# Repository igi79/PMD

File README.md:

PMD 85 
by Peter Chrenko: http://pmd85.topindex.sk/

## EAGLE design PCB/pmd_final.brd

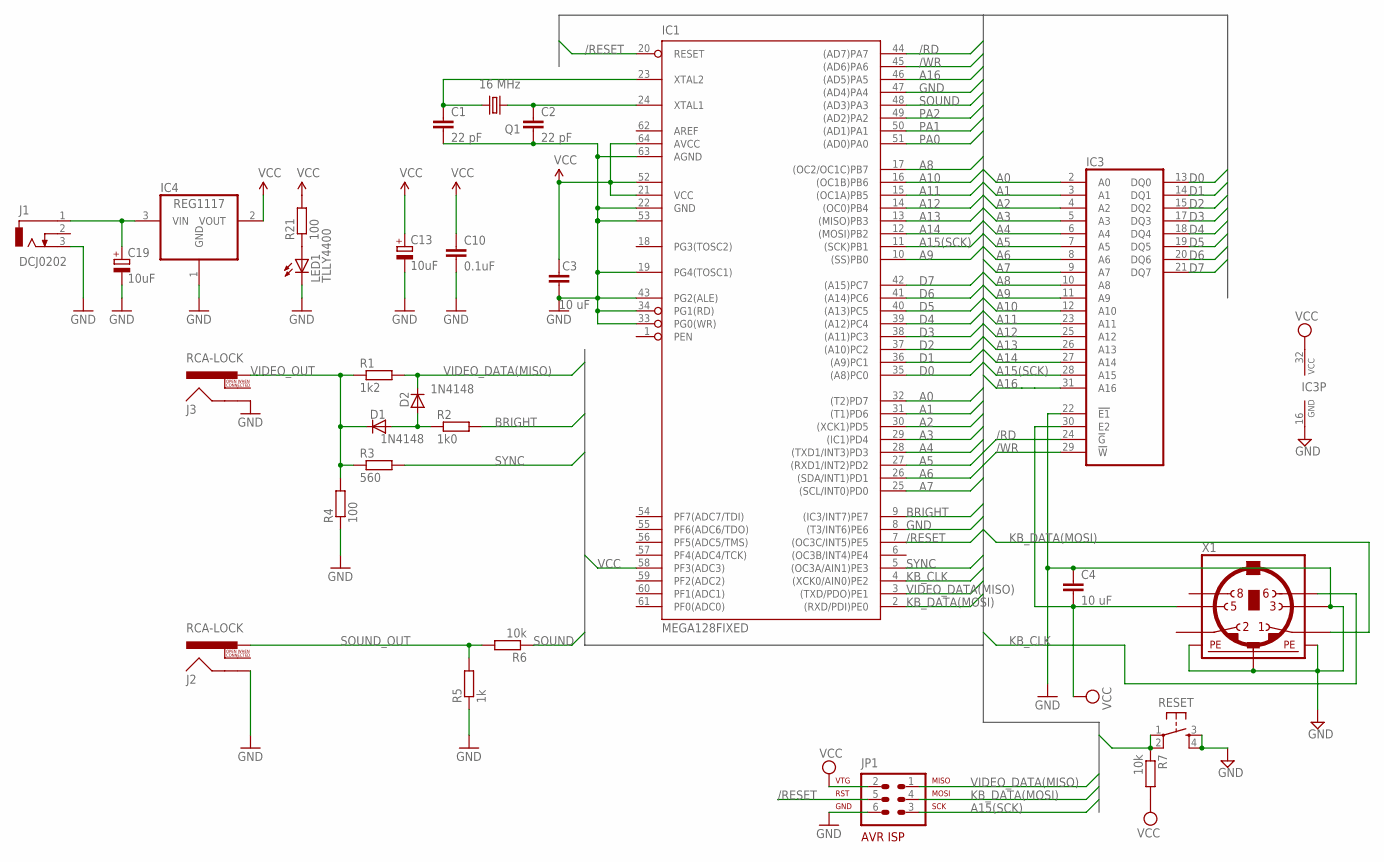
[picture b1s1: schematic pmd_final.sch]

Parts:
C1, C2: 22 pF; C0805
C3, C4: 10 uF; C0805
C10: 0.1uF; C0805
C13, C19: 10uF; E2,5-5
D1, D2: 1N4148; MINIMELF
IC1: MEGA128FIXED; TQFP64_14X14MM
IC3: MCM6226AULTRAWIDE; SOP32L
IC4: REG1117; SOT223
J1: DCJ0202
J2, J3: RCA-LOCK; RCA_LOCK
JP1: AVR-ISP-6R
LED1: TLLY4400; LED3MM
Q1: 16 MHz; HC49UP
R1: 1k2; R0805
R2: 1k0; R0805
R3: 560; R0805
R4, R21: 100; R0805
R5: 1k; R0805
R6, R7: 10k; R0805
RESET: RESET; TACTILE-PTH
X1: MINI_DIN_6; M_DIN6

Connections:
/RD: IC1.44 ((AD7)PA7), IC3.24 (!G)
/RESET: IC1.7 ((OC3C/INT5)PE5), IC1.20 (RESET), JP1.5, R7.1, RESET.1, RESET.2
/WR: IC1.45 ((AD6)PA6), IC3.29 (!W)
A0: IC1.32 ((T2)PD7), IC3.2 (A0)
A1: IC1.31 ((T1)PD6), IC3.3 (A1)
A2: IC1.30 ((XCK1)PD5), IC3.4 (A2)
A3: IC1.29 ((IC1)PD4), IC3.5 (A3)
A4: IC1.28 ((TXD1/INT3)PD3), IC3.6 (A4)
A5: IC1.27 ((RXD1/INT2)PD2), IC3.7 (A5)
A6: IC1.26 ((SDA/INT1)PD1), IC3.8 (A6)
A7: IC1.25 ((SCL/INT0)PD0), IC3.9 (A7)
A8: IC1.17 ((OC2/OC1C)PB7), IC3.10 (A8)
A9: IC1.10 ((SS)PB0), IC3.11 (A9)
A10: IC1.16 ((OC1B)PB6), IC3.12 (A10)
A11: IC1.15 ((OC1A)PB5), IC3.23 (A11)
A12: IC1.14 ((OC0)PB4), IC3.25 (A12)
A13: IC1.13 ((MISO)PB3), IC3.26 (A13)
A14: IC1.12 ((MOSI)PB2), IC3.27 (A14)
A15(SCK): IC1.11 ((SCK)PB1), IC3.28 (A15), JP1.3
A16: IC1.46 ((AD5)PA5), IC3.31 (A16)
BRIGHT: IC1.9 ((IC3/INT7)PE7), R2.2
D0: IC1.35 ((A8)PC0), IC3.13 (DQ0)
D1: IC1.36 ((A9)PC1), IC3.14 (DQ1)
D2: IC1.37 ((A10)PC2), IC3.15 (DQ2)
D3: IC1.38 ((A11)PC3), IC3.17 (DQ3)
D4: IC1.39 ((A12)PC4), IC3.18 (DQ4)
D5: IC1.40 ((A13)PC5), IC3.19 (DQ5)
D6: IC1.41 ((A14)PC6), IC3.20 (DQ6)
D7: IC1.42 ((A15)PC7), IC3.21 (DQ7)
GND: C1.2, C2.2, C3.1, C4.1, C10.2, C13.-, C19.-, IC1.8 ((T3/INT6)PE6), IC1.19 (PG4(TOSC1)), IC1.22 (GND), IC1.33 (PG0(WR)), IC1.34 (PG1(RD)), IC1.43 (PG2(ALE)), IC1.47 ((AD4)PA4), IC1.53 (GND1), IC1.63 (AGND), IC3.16 (GND), IC3.22 (!E1), IC4.1 (GND), J1.3, J2.SHELL, J3.SHELL, JP1.6, LED1.K (C), R4.1, R5.1, RESET.3, RESET.4, X1.3, X1.SH1 (PE1), X1.SH2 (PE2), X1.SH3 (PE3)
KB_CLK: IC1.4 ((XCK0/AIN0)PE2), X1.6
KB_DATA(MOSI): IC1.2 ((RXD/PDI)PE0), JP1.4, X1.1
unnamed: LED1.A, R21.1
unnamed: D1.A, D2.A, R2.1
PA0: IC1.51 ((AD0)PA0)
PA1: IC1.50 ((AD1)PA1)
PA2: IC1.49 ((AD2)PA2)
SOUND: IC1.48 ((AD3)PA3), R6.1
SOUND_OUT: J2.PIN, R5.2, R6.2
SYNC: IC1.5 ((OC3A/AIN1)PE3), R3.2
VCC: C3.2, C4.2, C10.1, C13.+, IC1.21 (VCC), IC1.52 (VCC1), IC1.58 (PF3(ADC3)), IC1.64 (AVCC), IC3.30 (E2), IC3.32 (VCC), IC4.2 (VOUT), JP1.2, R7.2, R21.2, X1.5
VIDEO_DATA(MISO): D2.C, IC1.3 ((TXD/PDO)PE1), JP1.1, R1.2
VIDEO_OUT: D1.C, J3.PIN, R1.1, R3.1, R4.2
VIN: C19.+, IC4.3 (VIN), J1.1
XTAL1: C2.1, IC1.24 (XTAL1), Q1.1
XTAL2: C1.1, IC1.23 (XTAL2), Q1.2

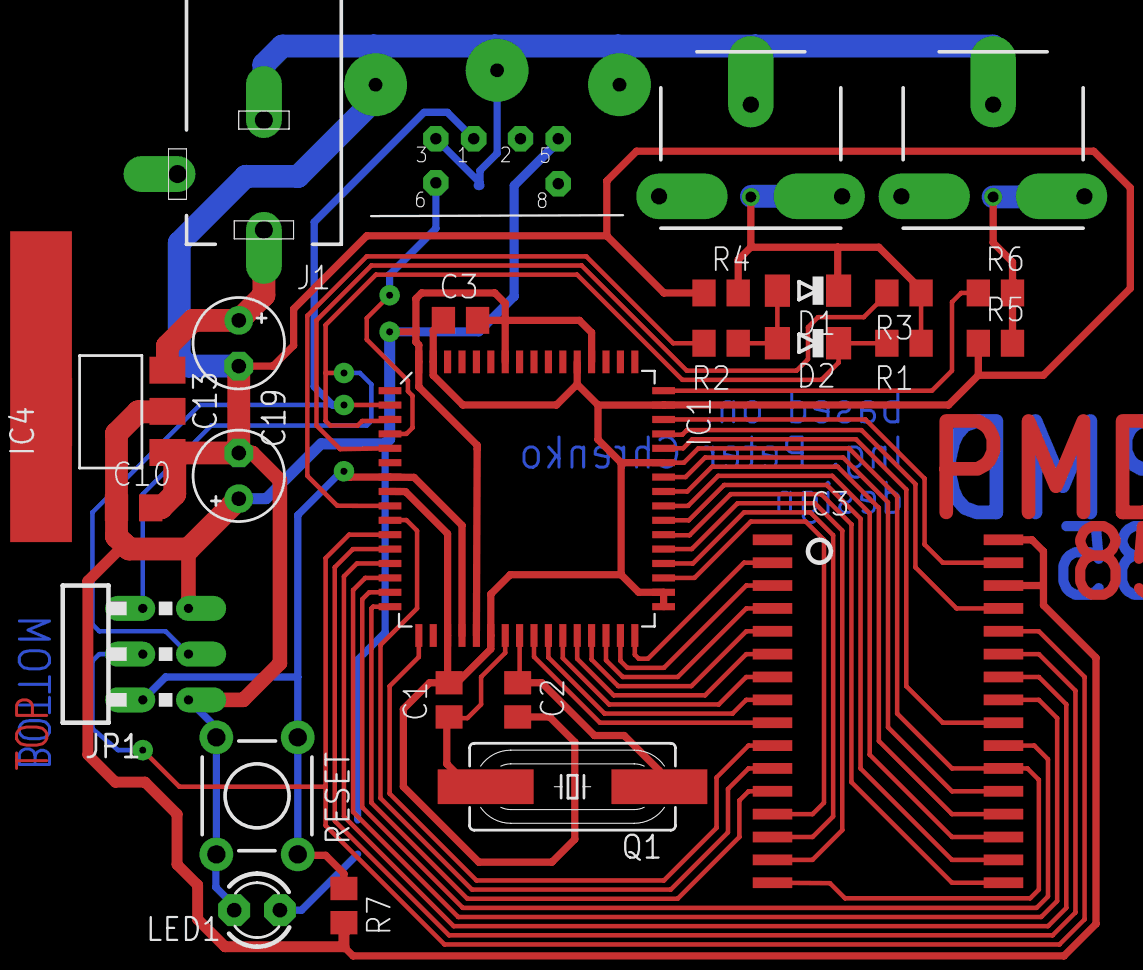
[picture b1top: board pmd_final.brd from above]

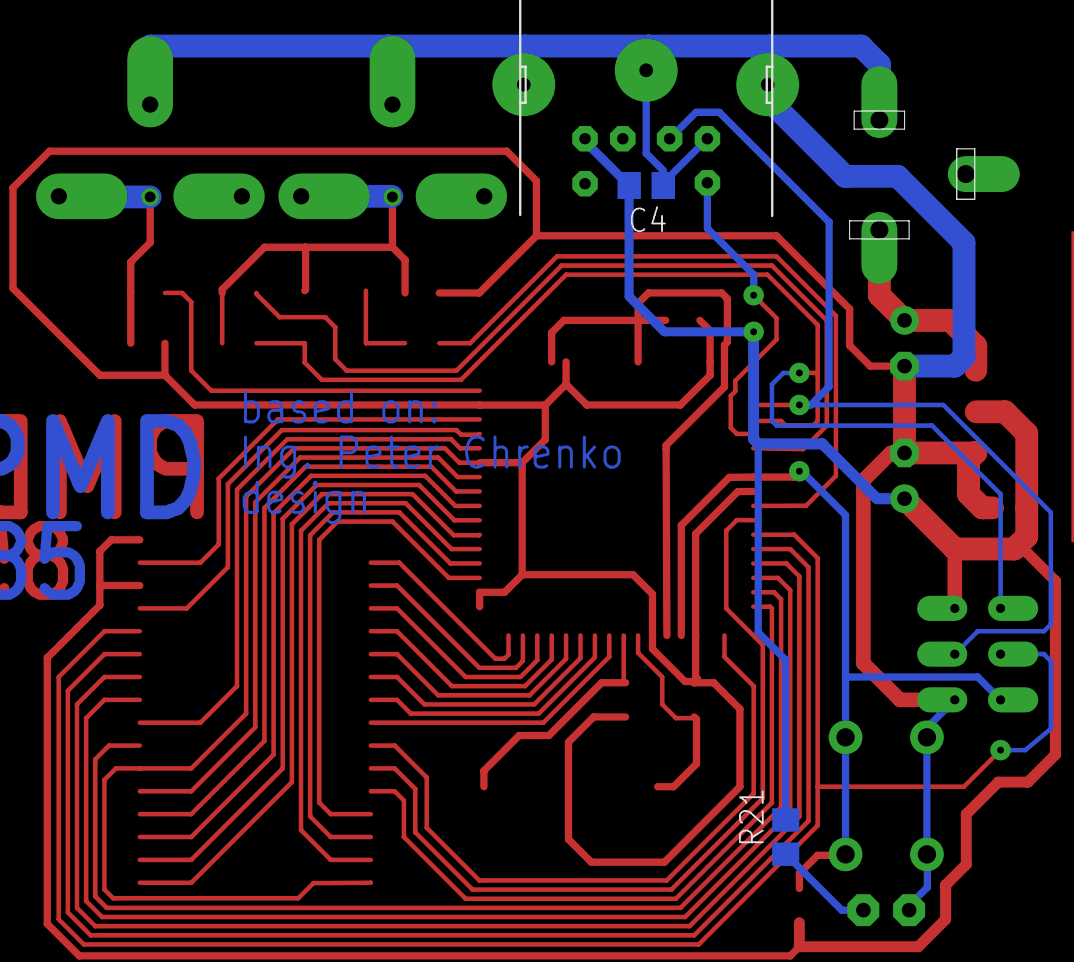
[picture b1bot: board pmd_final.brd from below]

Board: 2 copper layers, 28 parts (2 on the bottom side), 43 nets.

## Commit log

2016-03-19 Final
2016-03-20 PCB in PDF
2021-05-07 fixed 2021 version

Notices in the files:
parts and their libraries:
SparkFun-Connectors: Licensing: Creative Commons ShareAlike 4.0 International - https://creativecommons.org/licenses/by-sa/4.0
